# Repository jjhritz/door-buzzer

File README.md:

# door-buzzer
Audible buzzer for remotely-operated door lock

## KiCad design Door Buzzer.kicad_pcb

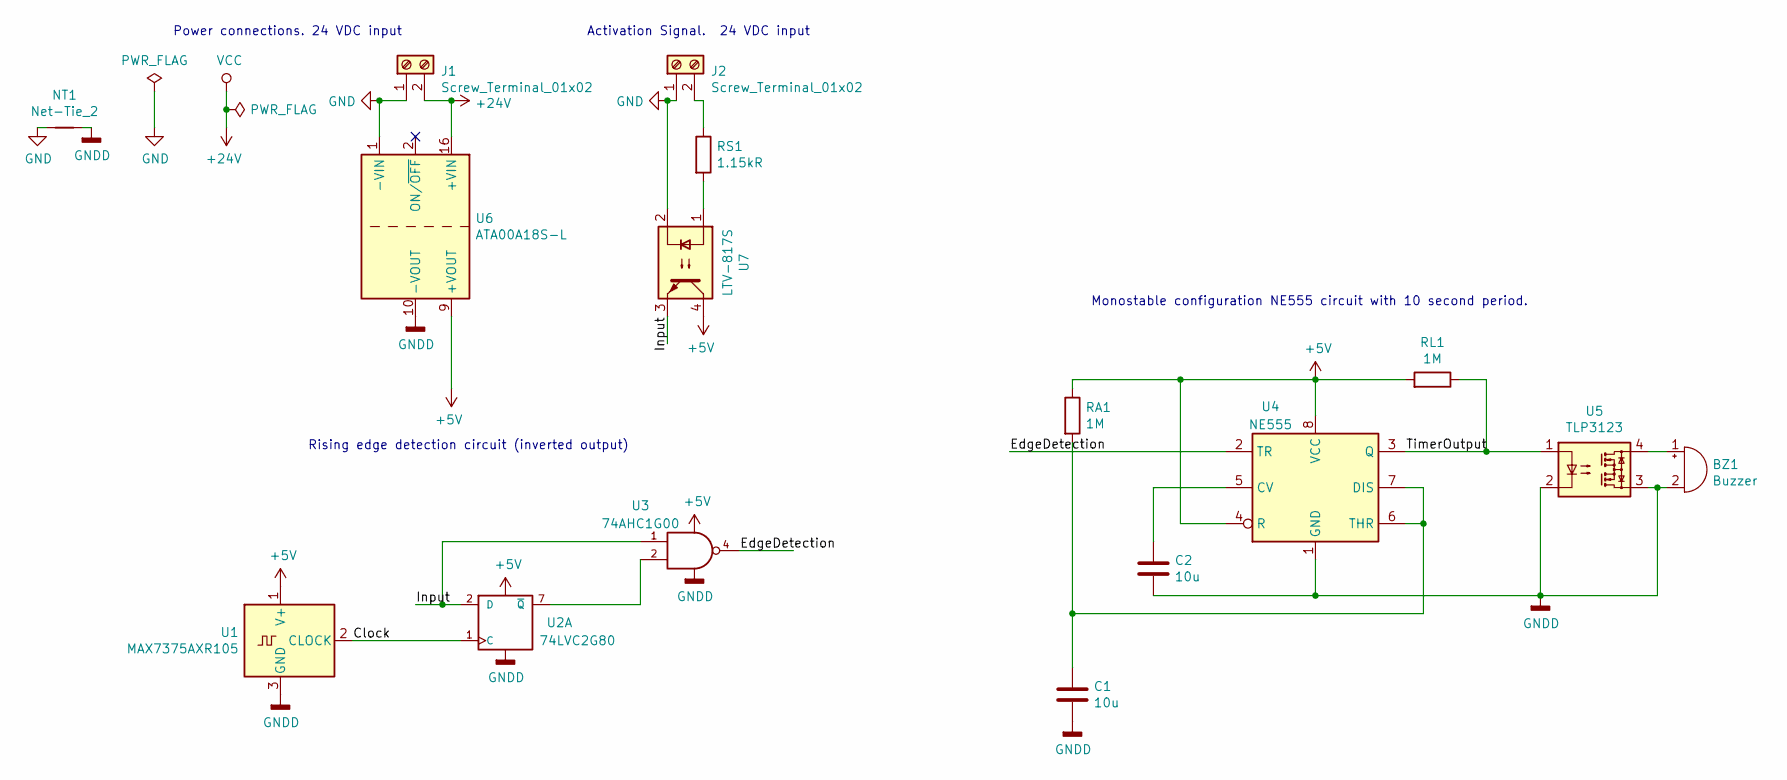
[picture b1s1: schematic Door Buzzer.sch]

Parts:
BZ1: Buzzer; CUI_CT-1205CL-SMT
C1, C2: 10u; C_0805_2012Metric
J1, J2: Screw_Terminal_01x02; TerminalBlock_4Ucon_1x02_P3.50mm_Horizontal
NT1: Net-Tie_2; NetTie-2_SMD_Pad0.5mm
RA1: 1M; R_0805_2012Metric
RL1: 1M; R_0805_2012Metric
RS1: 1.15kR; R_1210_3225Metric
U1: MAX7375AXR105; SOT-323_SC-70
U2: 74LVC2G80; SN74LVC2G80DCTR
U3: 74AHC1G00; SOT-353_SC-70-5
U4: NE555; SO-8_5.3x6.2mm_P1.27mm
U5: TLP3123; SO-4_4.4x3.9mm_P2.54mm
U6: ATA00A18S-L; Converter_DCDC_Artesyn_ATA_SMD
U7: LTV-817S; SMDIP-4_W9.53mm

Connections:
+5V: RA1.1, RL1.2, U1.1 (V+), U2.8 (+5V), U3.5 (+5V), U4.4 (R), U4.8 (VCC), U6.9 (+VOUT), U7.4
+24V: J1.2, U6.16 (+VIN)
/Clock: U1.2 (CLOCK), U2.1 (C)
/EdgeDetection: U3.4, U4.2 (TR)
/Input: U2.2 (D), U3.1, U7.3
/TimerOutput: RL1.1, U4.3 (Q), U5.1
GND: J1.1, J2.1, NT1.2, U6.1 (-VIN), U7.2
GNDD: BZ1.2 (+), C1.2, C2.2, NT1.1, U1.3 (GND), U2.4 (GNDD), U3.3 (GNDD), U4.1 (GND), U5.2, U5.3, U6.10 (-VOUT)
unnamed: BZ1.1 (-), U5.4
unnamed: C1.1, RA1.2, U4.6 (THR), U4.7 (DIS)
unnamed: C2.1, U4.5 (CV)
unnamed: J2.2, RS1.1
unnamed: RS1.2, U7.1
unnamed: U2.7 (~Q), U3.2

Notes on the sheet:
Monostable configuration NE555 circuit with 10 second period.
Rising edge detection circuit (inverted output)
Power connections. 24 VDC input
Activation Signal. 24 VDC input

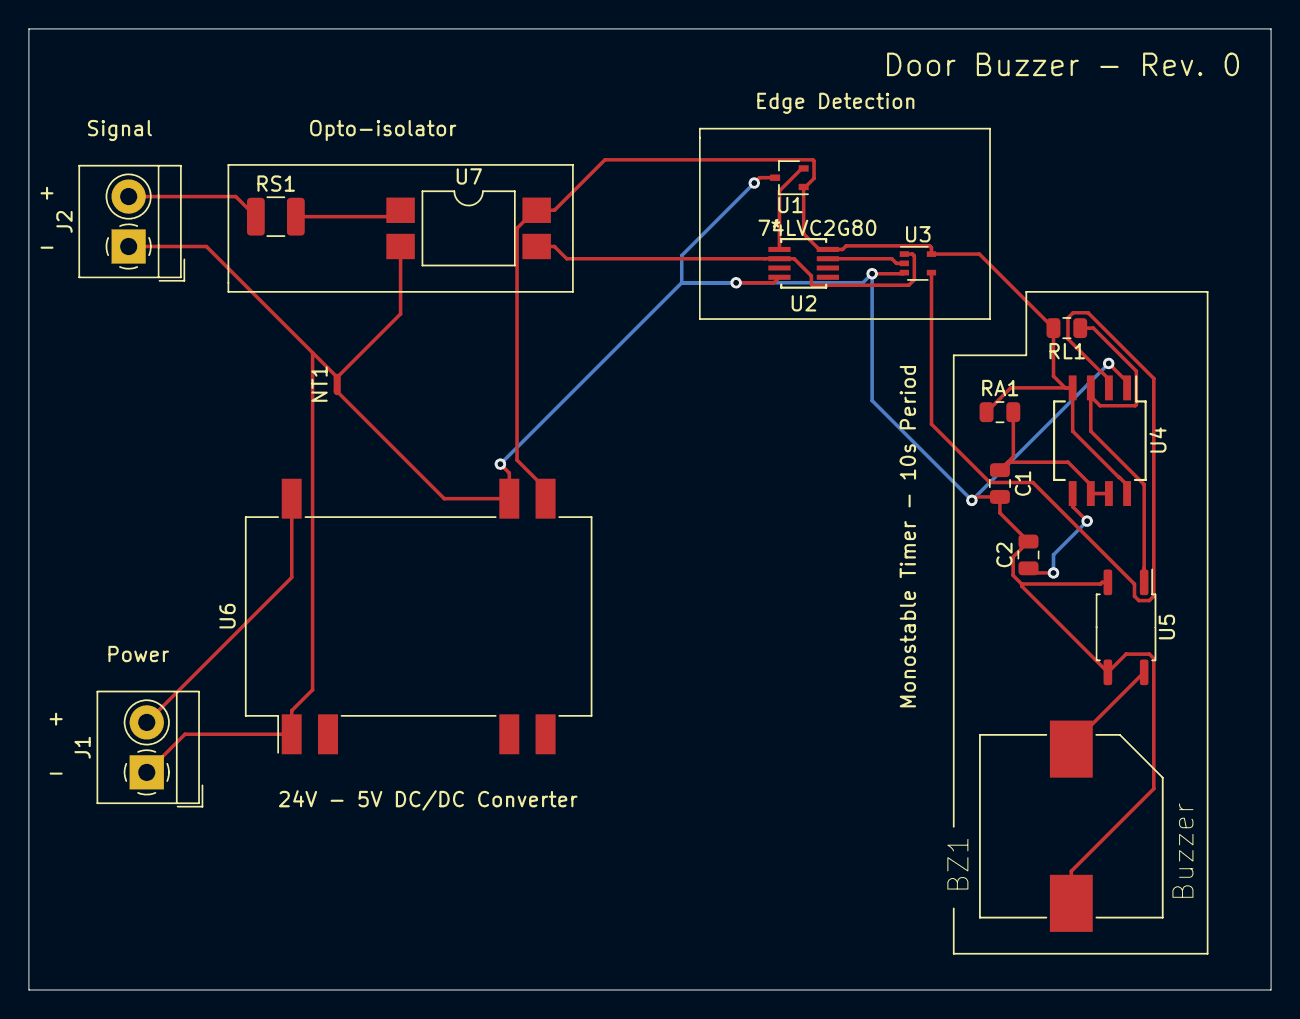
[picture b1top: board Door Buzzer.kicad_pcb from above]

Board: 2 copper layers, 87.0 x 67.3 mm, 16 parts (0 on the bottom side), 14 nets.

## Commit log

2019-07-29 Initial commit of rev. 0

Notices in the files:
parts and their libraries:
Copyright 2016 Accelerated Designs. All rights reserved.
